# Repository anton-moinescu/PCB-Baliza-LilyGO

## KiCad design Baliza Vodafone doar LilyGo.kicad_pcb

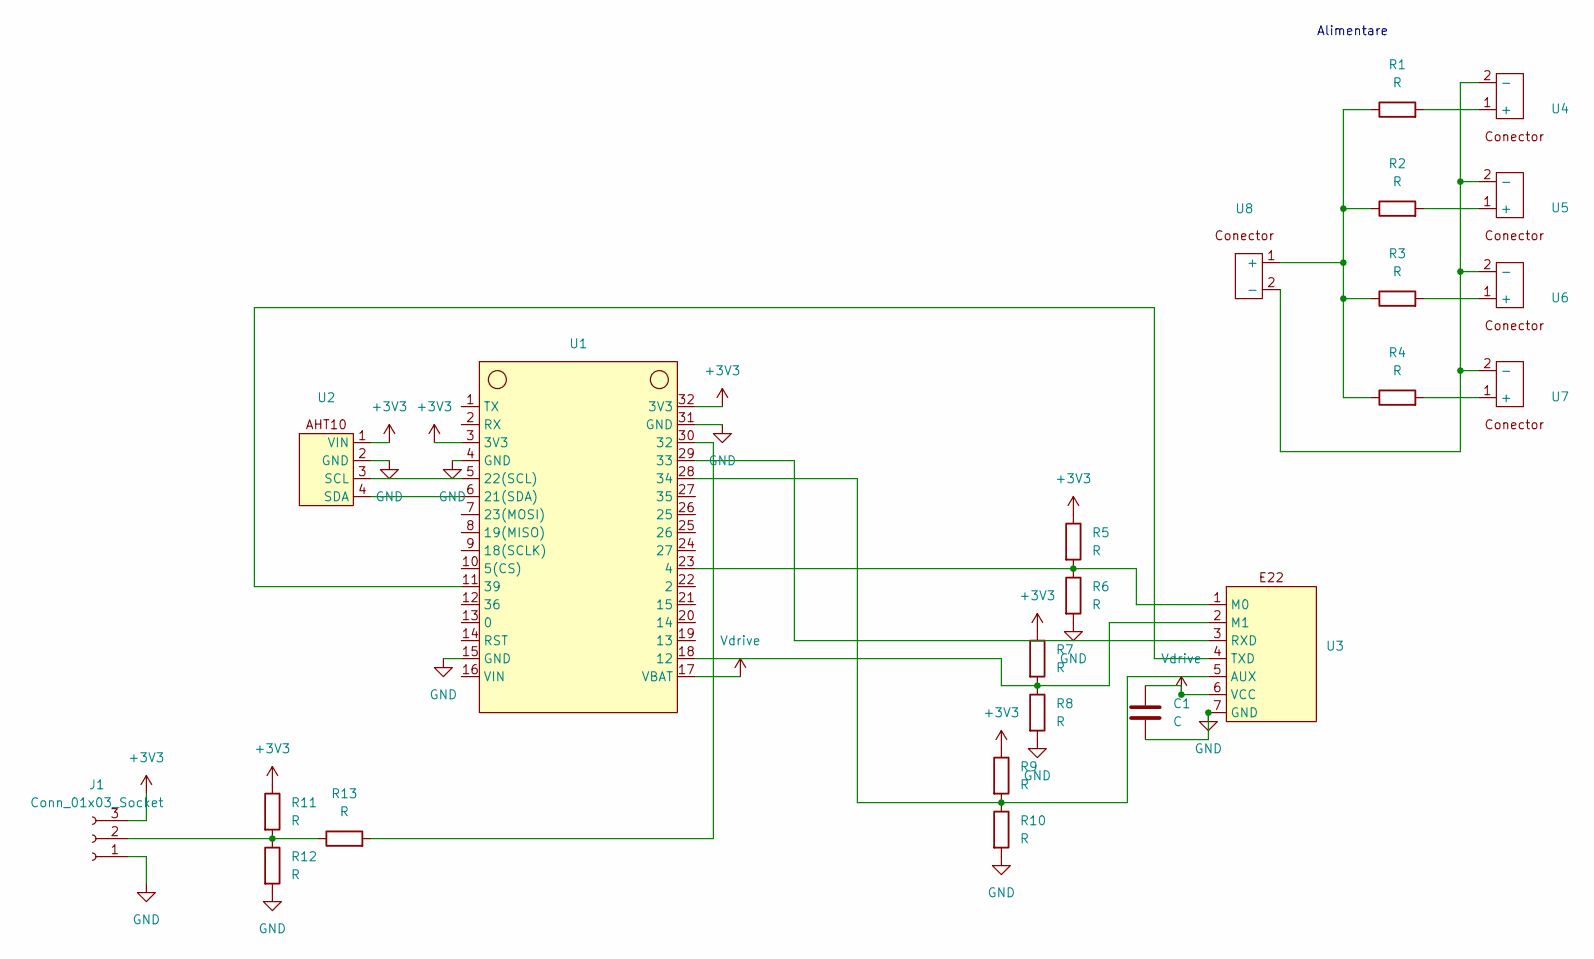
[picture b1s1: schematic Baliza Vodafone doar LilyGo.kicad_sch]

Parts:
C1: C; CP_Radial_D5.0mm_P2.50mm
J1: Conn_01x03_Socket; PinSocket_1x03_P2.54mm_Vertical
R1, R2, R3, R4: R; R_Axial_DIN0204_L3.6mm_D1.6mm_P7.62mm_Horizontal
R5, R6, R7, R8, R9, R10, R11, R12, R13: R; R_1206_3216Metric_Pad1.30x1.75mm_HandSolder
U1: Lilygo ESP-32
U2: AHT10
U3: Modul E22- ambele modele
U4, U5, U6, U7, U8: PinHeader_1x02_P2.54mm_Horizontal

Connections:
+3V3: J1.3, R5.1, R7.1, R9.1, R11.1, U1.3 (3V3), U1.32 (3V3), U2.1 (VIN)
GND: C1.2, J1.1, R6.2, R8.2, R10.2, R12.2, U1.4 (GND), U1.15 (GND), U1.31 (GND), U2.2 (GND), U3.7 (GND)
unnamed: J1.2, R11.2, R12.1, R13.1
unnamed: R5.2, R6.1, U1.23 (4), U3.1 (M0)
unnamed: R7.2, R8.1, U1.18 (12), U3.2 (M1)
unnamed: U1.6 (21(SDA)), U2.4 (SDA)
unnamed: U1.5 (22(SCL)), U2.3 (SCL)
unnamed: R13.2, U1.30 (32)
unnamed: U1.29 (33), U3.3 (RXD)
unnamed: R9.2, R10.1, U1.28 (34), U3.5 (AUX)
unnamed: U1.11 (39), U3.4 (TXD)
unnamed: R1.2, U4.1 (+)
unnamed: U4.2 (-), U5.2 (-), U6.2 (-), U7.2 (-), U8.2 (-)
unnamed: R2.2, U5.1 (+)
unnamed: R3.2, U6.1 (+)
unnamed: R4.2, U7.1 (+)
unnamed: R1.1, R2.1, R3.1, R4.1, U8.1 (+)
Vdrive: C1.1, U1.17 (VBAT), U3.6 (VCC)

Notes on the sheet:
Alimentare

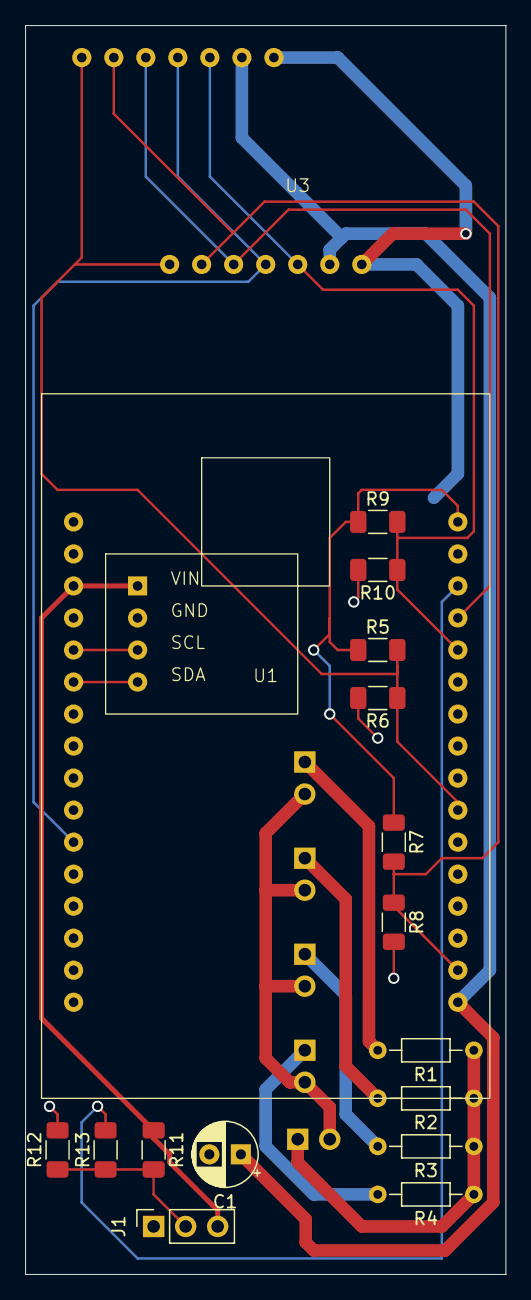
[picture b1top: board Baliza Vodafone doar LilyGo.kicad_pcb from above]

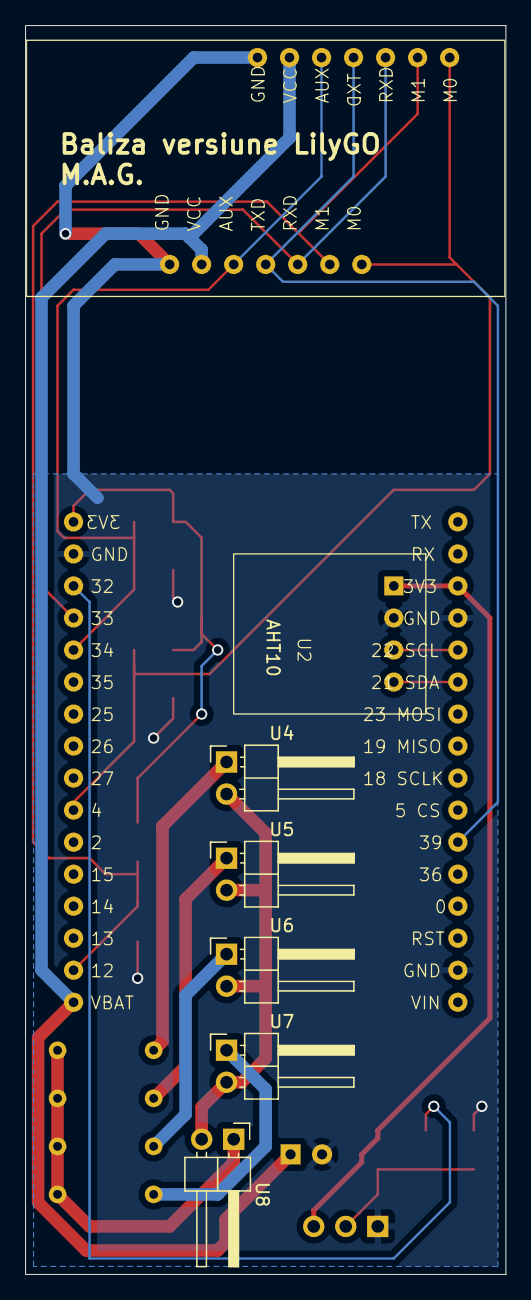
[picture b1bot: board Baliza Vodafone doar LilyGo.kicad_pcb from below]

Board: 2 copper layers, 38.1 x 99.1 mm, 23 parts (7 on the bottom side), 18 nets.
